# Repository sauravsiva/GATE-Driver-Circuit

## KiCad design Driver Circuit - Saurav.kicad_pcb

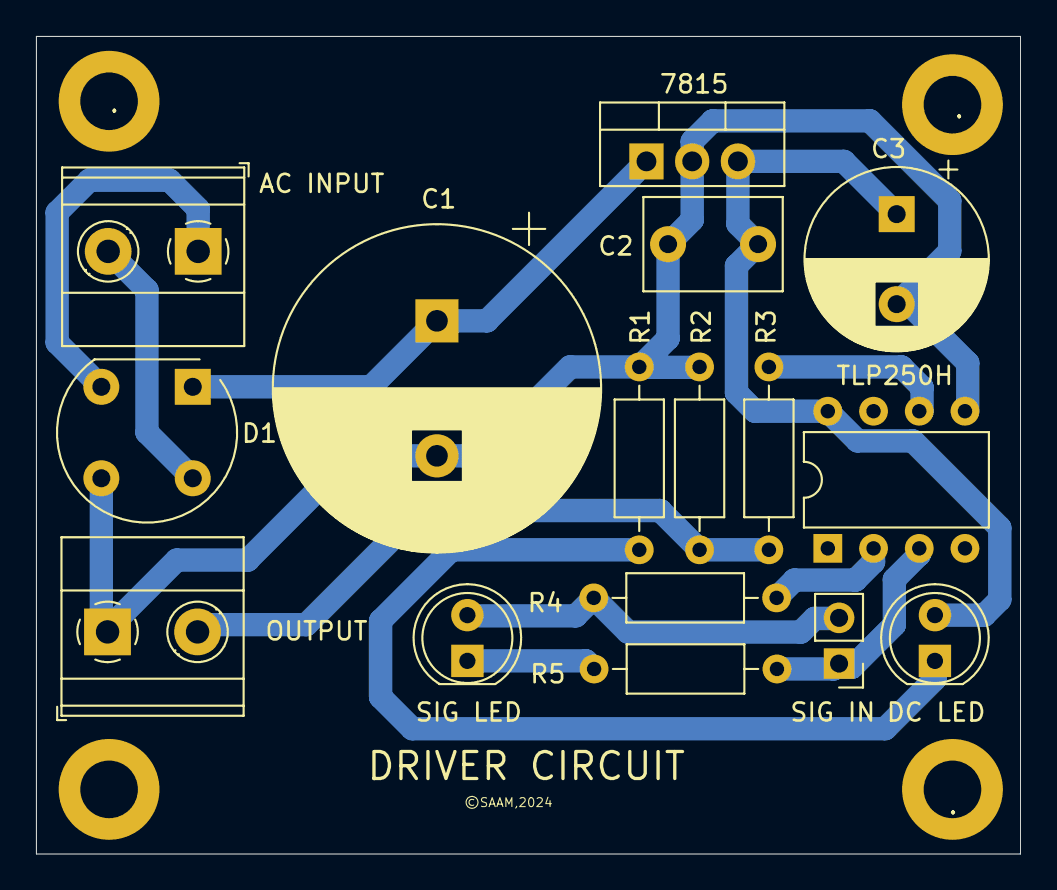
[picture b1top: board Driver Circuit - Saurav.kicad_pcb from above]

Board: 2 copper layers, 54.7 x 45.4 mm, 20 parts (0 on the bottom side), 12 nets.

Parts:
7815: L7815; TO-220-3_Vertical
., .#2, .#3, .#4: MountingHole_3.2mm_M3_DIN965_Pad
AC INPUT: Screw_Terminal_01x02; TerminalBlock_Phoenix_MKDS-1,5-2_1x02_P5.00mm_Horizontal
C1: 2200uF 50V; CP_Radial_D18.0mm_P7.50mm
C2: 0.1uF; C_Disc_D7.5mm_W5.0mm_P5.00mm
C3: 220uF 50V; CP_Radial_D10.0mm_P5.00mm
D1: W10G; Diode_Bridge_Round_D9.8mm
DC LED: LED; LED_D5.0mm
OUTPUT: Screw_Terminal_01x02; TerminalBlock_Phoenix_MKDS-1,5-2_1x02_P5.00mm_Horizontal
R1: 2.2k; R_Axial_DIN0207_L6.3mm_D2.5mm_P10.16mm_Horizontal
R2: 10K; R_Axial_DIN0207_L6.3mm_D2.5mm_P10.16mm_Horizontal
R3: 10E; R_Axial_DIN0207_L6.3mm_D2.5mm_P10.16mm_Horizontal
R4: 220E; R_Axial_DIN0207_L6.3mm_D2.5mm_P10.16mm_Horizontal
R5: 2.2K; R_Axial_DIN0207_L6.3mm_D2.5mm_P10.16mm_Horizontal
SIG IN: Conn_01x02_Pin; PinHeader_1x02_P2.54mm_Vertical
SIG LED: LED; LED_D5.0mm
TLP250H: TLP250; DIP-8_W7.62mm

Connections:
GND: 7815.2 (GND), C1.2, C2.2, C3.2, D1.3 (-), OUTPUT.1, R1.2, R2.2, TLP250H.5 (VEE)
GND1: R5.2, SIG IN.1, TLP250H.3 (C)
unnamed: 7815.1 (IN), C1.1, D1.1 (+)
unnamed: 7815.3 (OUT), C2.1, C3.1, DC LED.2 (A), TLP250H.8 (VCC)
unnamed: DC LED.1 (K), R1.1
unnamed: R4.2, SIG IN.2, SIG LED.2 (A)
unnamed: R5.1, SIG LED.1 (K)
unnamed: AC INPUT.1, D1.2
unnamed: AC INPUT.2, D1.4
unnamed: OUTPUT.2, R2.1, R3.1
unnamed: R3.2, TLP250H.6 (VO)
unnamed: R4.1, TLP250H.2 (A)

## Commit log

2025-01-18 Changed File Names
2025-01-18 Change File Names, removed Backups Folder
2025-01-18 Added files for 4 channel and 1 channel driver circuits
2025-01-18 Removing Unwanted Files
2025-01-18 Editing gitignore
2025-01-18 Removed Unwanted Files, Renamed Files for Clarity

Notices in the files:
Driver Circuit - Saurav.kicad_pcb:
©SAAM,2024
